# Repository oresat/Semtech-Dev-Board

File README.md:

# Development board for the Semtech SX1236

## UPDATE: THIS PROJECT HAS BEEN DEPRECATED (RETIRED)

Because of the difficulty of getting the SX1236 to reliably work, we moved on to the On Semi AX5043. This project is now retired and won't be worked on any more.

-----

## Overview

OreSat is designed around a 70 cm (436 MHz) radio system for what other cubesats call their Command and Data Handling (C&DH) system. We started with the NXP Kw0x series chips but found that chip, and it's interface to its embedded Semtech SX1232 (?) radio IC, too painful to continue. 

Since the specs on the Semtech radio ICs are good, we could "upgrade" a generation by going to a separate IC, and we're interesting in using a STM32 for our system controller, we decided on using the SX1236. Of *course* no one makes an evaluation board for this IC. Sigh.

## Firmware

The current firmware to test this board is located in the [devsat repo under app_semtech](https://github.com/oresat/devsat/tree/master/firmware/chib_stf4x/src/app_semtech).

## Requirements

- Must be a barebones, "development" or "evaluation" board for the SX1236.
- Must work under USB and LiPo power
- Open source

## Specifications

- Must
   - RF out via Female SMA connector (board edge preferred)
   - Must have a 0.1" pinheader for power and control signals.
   - All but NC pads must be broken out to test points with vias for easy modding
   - Voltage input range of 3.0 to 5.5 V.
   - Use 0.1" headers and jumpers for configuration pins
- Should
   - Have large square silk screen area for board #
   - Have copper ground pads around edge of  board for scope clips
- Must not
   - Feature creep (don't go nuts, just make us an evaluation board of a refernece design)
   - This includes not bothering to deal with LNAs or PAs for this board! It's local only.

## References

- [Original Practicum Kw0x Development board](https://github.com/wrh2/sputnik/tree/master/Phase0/eagle)
- Original OreSat [Low Gain Radio board](https://github.com/oresat/low-gain-radio)
- [Semtech SX126 Webpage](http://www.semtech.com/wireless-rf/rf-transceivers/sx1236/)
- The [SX1276](http://www.semtech.com/apps/product.php?pn=SX1276) may have the same pinout, but also has a LoRa radio built in (blech)

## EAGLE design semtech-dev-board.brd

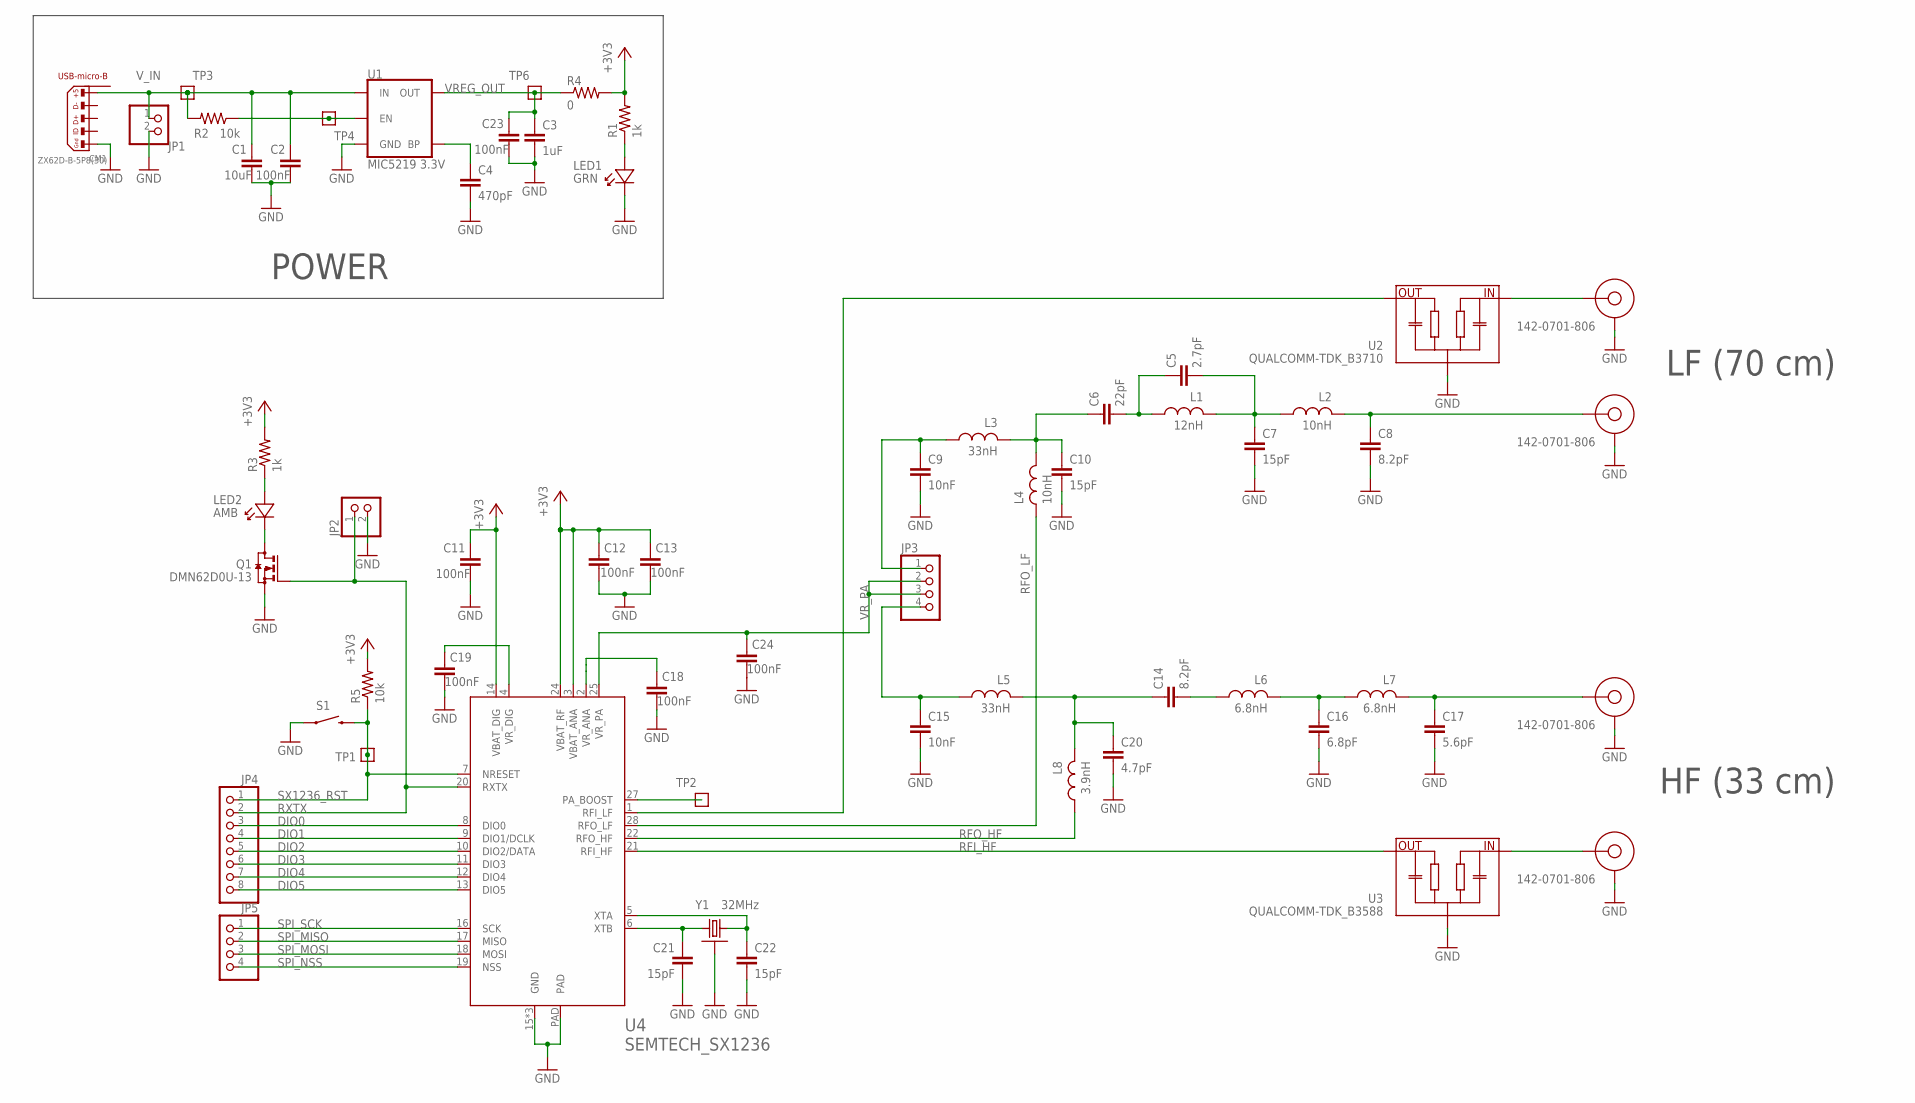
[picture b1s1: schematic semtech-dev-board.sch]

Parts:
C1: 10uF; .0805-B
C2, C11, C12, C13, C18, C19, C23, C24: 100nF; .0603-B-NOSILK
C3: 1uF; .0603-B-NOSILK
C4: 470pF; .0603-B-NOSILK
C5: 2.7pF; .0603-B-NOSILK
C6: 22pF; .0603-B-NOSILK
C7, C10, C21, C22: 15pF; .0603-B-NOSILK
C8, C14: 8.2pF; .0603-B-NOSILK
C9, C15: 10nF; .0603-B-NOSILK
C16: 6.8pF; .0603-B-NOSILK
C17: 5.6pF; .0603-B-NOSILK
C20: 4.7pF; .0603-B-NOSILK
CF1, CF2, CF3, CF4: 142-0701-806; SMAJ716-ND
CM1: ZX62D-B-5P8(30); USB-MICRO-B-PTH-HIROSE
JP1, JP2: PINHD-1X2; 1X02
JP3, JP5: PINHD-1X4; 1X04
JP4: PINHD-1X8; 1X08
L1: 12nH; .0603-B-NOSILK
L2, L4: 10nH; .0603-B-NOSILK
L3, L5: 33nH; .0603-B-NOSILK
L6, L7: 6.8nH; .0603-B-NOSILK
L8: 3.9nH; .0603-B-NOSILK
LED1: GRN; LED-0603
LED2: AMB; LED-0603
Q1: DMN62D0U-13; SOT23
R1, R3: 1k; .0603-B-NOSILK
R2, R5: 10k; .0603-B-NOSILK
R4: 0; .0603-B-NOSILK
S1: FSM4JSMATR; TACTILE_SWITCH_SMD-2
TP1, TP2, TP3, TP4, TP6: TEST-POINT; 2MM-TEST-POINT
U1: MIC5219 3.3V; SOT23-5
U2: QUALCOMM-TDK_B3710; DCC6C-EPCOS
U3: QUALCOMM-TDK_B3588; DCC6C-EPCOS
U4: SEMTECH_SX1236; QFN28
Y1: 32MHz; CRYSTAL_2.5X2

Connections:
+3V3: C11.1, C12.1, C13.1, R1.2, R3.2, R4.2, R5.2, U4.3 (VBAT_ANA), U4.14 (VBAT_DIG), U4.24 (VBAT_RF)
BP: C4.1, U1.4 (BP)
DIO0: JP4.3, U4.8 (DIO0)
DIO1: JP4.4, U4.9 (DIO1/DCLK)
DIO2: JP4.5, U4.10 (DIO2/DATA)
DIO3: JP4.6, U4.11 (DIO3)
DIO4: JP4.7, U4.12 (DIO4)
DIO5: JP4.8, U4.13 (DIO5)
GND: C1.2, C2.2, C3.2, C4.2, C7.2, C8.2, C9.2, C10.2, C11.2, C12.2, C13.2, C15.2, C16.2, C17.2, C18.2, C19.2, C20.2, C21.2, C22.2, C23.2, C24.2, CF1.GND1 (GND), CF1.GND2 (GND), CF1.GND3 (GND), CF1.GND4 (GND), CF2.GND1 (GND), CF2.GND2 (GND), CF2.GND3 (GND), CF2.GND4 (GND), CF3.GND1 (GND), CF3.GND2 (GND), CF3.GND3 (GND), CF3.GND4 (GND), CF4.GND1 (GND), CF4.GND2 (GND), CF4.GND3 (GND), CF4.GND4 (GND), CM1.5, JP1.2, JP2.2, LED1.K, Q1.2 (S), S1.2 (1), U1.2 (GND), U2.1 (GND), U2.3 (GND), U2.4 (GND), U2.6 (GND), U3.1 (GND), U3.3 (GND), U3.4 (GND), U3.6 (GND), U4.15 (GND), U4.23 (GND), U4.26 (GND), U4.PAD, Y1.2 (SHIELD), Y1.4 (SHIELD)
HFO_PA_HEAD: C15.1, JP3.4, L5.2
LED+: LED2.A, R3.1
LED-: LED2.K, Q1.3 (D)
LFO_PA_HEAD: C9.1, JP3.1, L3.2
unnamed: R2.1, TP4.1, U1.3 (EN)
unnamed: CF4.P$3 (CENTERCONDUCTOR), U3.2 (IN)
unnamed: CF1.P$3 (CENTERCONDUCTOR), U2.2 (IN)
unnamed: LED1.A, R1.1
PA_BOOST: TP2.1, U4.27 (PA_BOOST)
RFI_HF: U3.5 (OUT), U4.21 (RFI_HF)
RFI_LF: U2.5 (OUT), U4.1 (RFI_LF)
RFO_HF: L8.2, U4.22 (RFO_HF)
RFO_HF_1: C14.2, L6.2
RFO_HF_2: C16.1, L6.1, L7.2
RFO_HF_OUT: C17.1, CF3.P$3 (CENTERCONDUCTOR), L7.1
RFO_HF_PA: C14.1, C20.1, L5.1, L8.1
RFO_LF: L4.1, U4.28 (RFO_LF)
RFO_LF_1: C5.1, C6.2, L1.2
RFO_LF_2: C5.2, C7.1, L1.1, L2.2
RFO_LF_OUT: C8.1, CF2.P$3 (CENTERCONDUCTOR), L2.1
RFO_LF_PA: C6.1, C10.1, L3.1, L4.2
RXTX: JP2.1, JP4.2, Q1.1 (G), U4.20 (RXTX)
SPI_MISO: JP5.2, U4.17 (MISO)
SPI_MOSI: JP5.3, U4.18 (MOSI)
SPI_NSS: JP5.4, U4.19 (NSS)
SPI_SCK: JP5.1, U4.16 (SCK)
SX1236_RST: JP4.1, R5.1, S1.1 (2), TP1.1, U4.7 (NRESET)
VREG_OUT: C3.1, C23.1, R4.1, TP6.1, U1.5 (OUT)
VR_ANA: C18.1, U4.2 (VR_ANA)
VR_DIG: C19.1, U4.4 (VR_DIG)
VR_PA: C24.1, JP3.2, JP3.3, U4.25 (VR_PA)
V_IN: C1.1, C2.1, CM1.1, JP1.1, R2.2, TP3.1, U1.1 (IN)
XTALA: C22.1, U4.5 (XTA), Y1.3 (2)
XTALB: C21.1, U4.6 (XTB), Y1.1

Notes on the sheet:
POWER
LF (70 cm)
HF (33 cm)

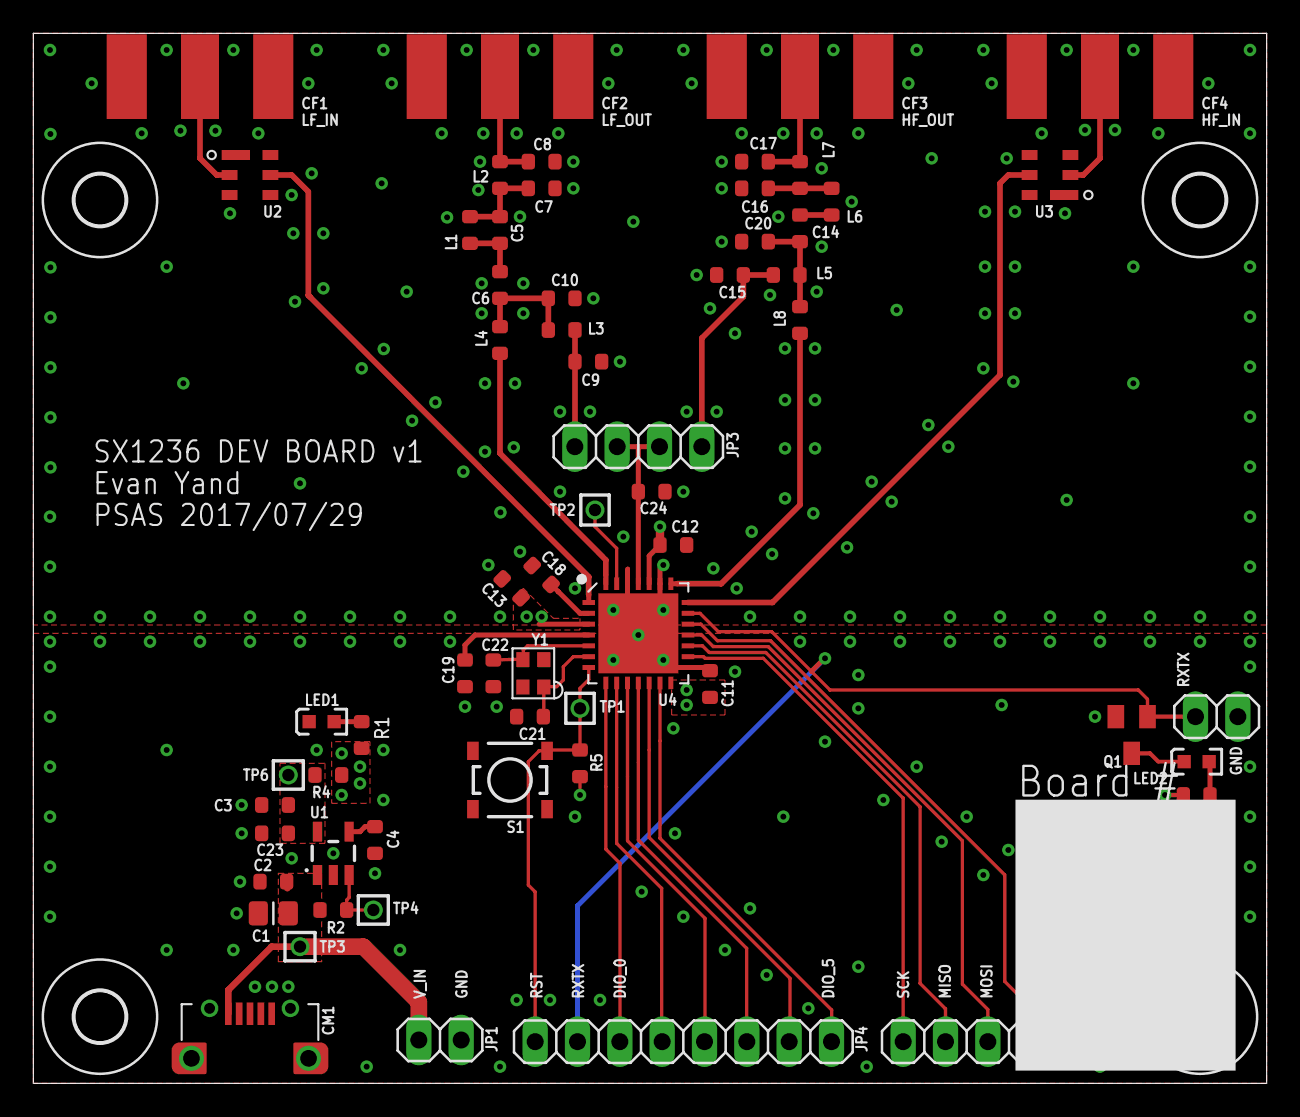
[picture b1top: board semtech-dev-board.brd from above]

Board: 4 copper layers, 74.0 x 63.0 mm, 75 parts (0 on the bottom side), 43 nets.

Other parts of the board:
U$1, U$2, U$3, U$5, U$6, U$7, U$12, U$13, U$14, U$15: SCOPE_CLIP
U$8, U$9, U$10, U$11: 3,0

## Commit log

2017-07-03 Some requirements to get you going.
2017-07-03 Update README.md
    Oh, right, no LNAs or PAs please.
2017-07-03 Aha, found the old practicum board.
2017-07-03 Started schematic
2017-07-03 started on power
2017-07-03 added vreg
2017-07-03 created brd file
2017-07-05 Connected power supply
2017-07-05 named nets
2017-07-05 Fixed bus
2017-07-09 adjustments based on Friday meeting
2017-07-09 Updates from Sunday meeting
2017-07-10 added biasing circuitry to match ref design for sx1233
2017-07-12 formatted sch
2017-07-12 started 4 layer board
2017-07-13 Fixed inductors
2017-07-14 Draft arrangement of components
2017-07-14 board draft
2017-07-14 minor edits
2017-07-19 started routing, adjusted placement, named nets
2017-07-21 Removed caps
2017-07-24 Components placed, 80% routed
2017-07-25 97% routed, needs vias, mounts, scope clips, and vals
2017-07-25 Filter values updated
2017-07-26 Tuesday D/R
2017-07-26 reworked board based on feedback, needs mounting holes
2017-07-27 added holes
2017-07-30 Board clean up from Evan's excellent first draft. Fixed SMA connectors, SAW filters, and 1236 packages. Made sure passives were from rlc_custom. More stiching, isolate on polygons, added a mounting h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
2017-07-30 TNAMES cleanup, better ground plane splitting - probably TOTALLY unnecessary on this board, but whatevs, it's fun. Updated SX1236 symbol, switched digital/analog caps to be correct.
2017-07-30 Added cap to VR_PA, because it said to. Probably overkill, given the other ones.
2017-07-31 Added updated BOM, and adjusted inductor sizes
2017-07-31 reformatted BOM
2017-07-31 added place column to bom
2017-07-31 New format for BOM; still needs parts chosen.
2017-07-31 Chose parts and added Digikey part numbers to BoM, switched inductors to 0603 because it was easy, shrunk board by 3 mm, cleaned up stapling, switched LEDs to 0603, oh and added a power LED for fun.
2017-07-31 Tent vias. They're all ground anyway, so might as well make it easy to solder and not blow up.
2017-07-31 Added stencil file for reference.
2017-07-31 Whoah - almost missed the fixed to the crystal from the LGR board. Kenny would have totally killed us all.
2017-08-03 added link to firmware directory in devsat
2017-08-25 Started a testing strategy document
2017-08-25 Some corrections to testing strategy document
2017-08-28 More updates to testing strategy document
2017-09-06 Added semtech-dev-board-registers.h which contains intended register contents for initial testing
2017-09-10 Added spreadsheet describing register details and updated semtech-dev-board-registers.h to reflect changes.
2017-09-26 added pdfs of eagle schematics
2019-01-15 Note on retirement.

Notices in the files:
parts and their libraries:
SparkFun-IC-Power: Licensing: Creative Commons ShareAlike 4.0 International - https://creativecommons.org/licenses/by-sa/4.0
